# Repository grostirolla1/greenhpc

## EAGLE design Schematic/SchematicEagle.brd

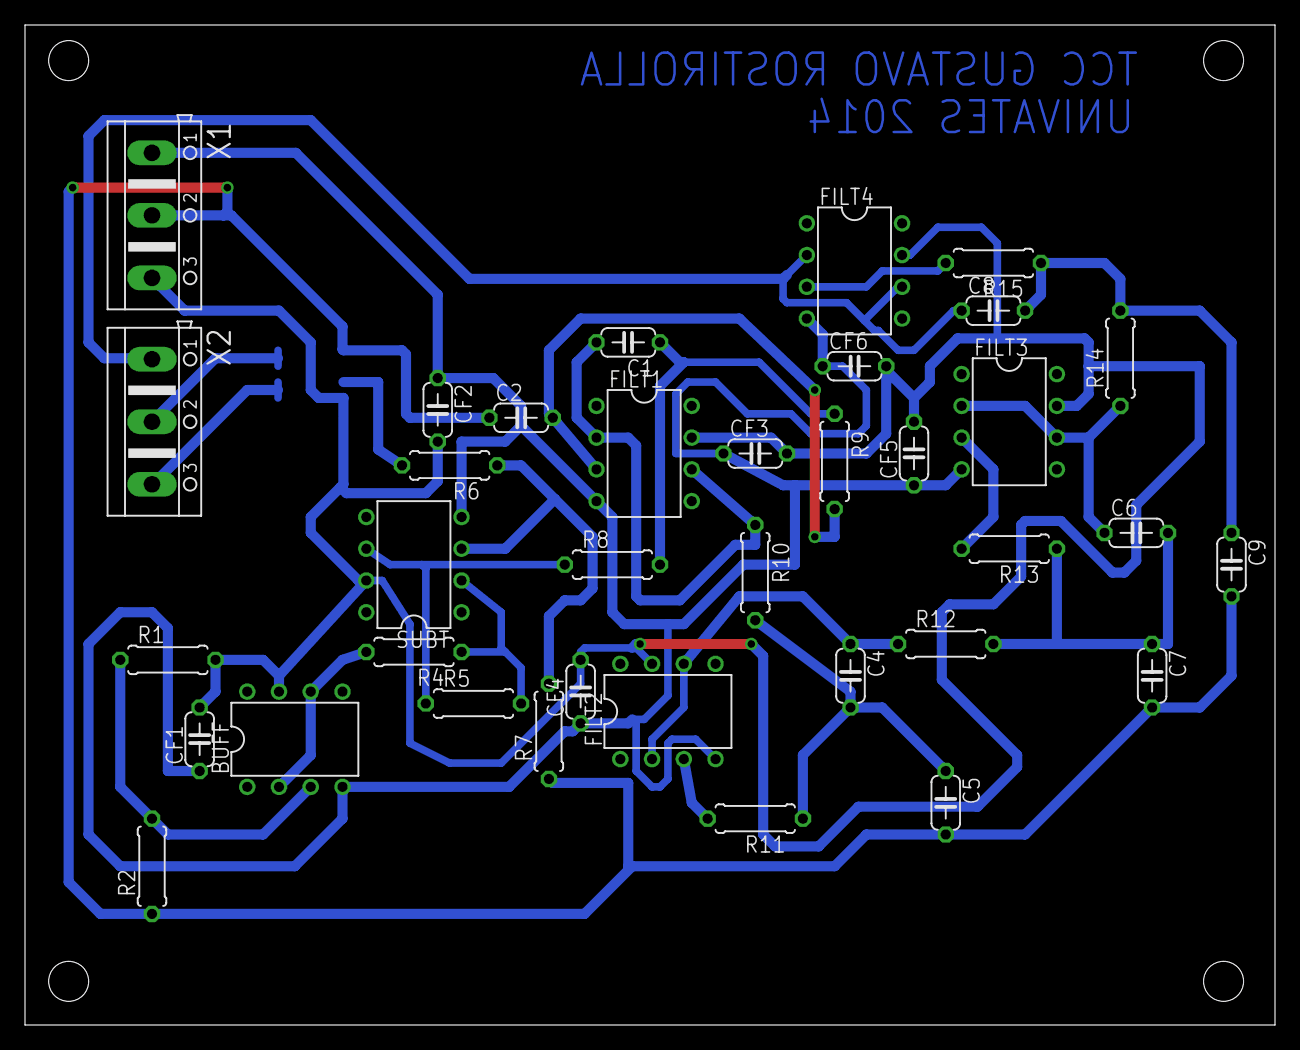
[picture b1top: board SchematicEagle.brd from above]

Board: 2 copper layers, 100.0 x 80.0 mm, 37 parts (1 on the bottom side), 23 nets.

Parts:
BUFF: OP07DN; DIL08
C1, C4: 15nF; C050-024X044
C2, C5, C7, C9: 10nF; C050-024X044
C6: 33nF; C050-024X044
C8: 330nF; C050-024X044
CF1, CF2, CF3, CF4, CF5, CF6: 100nF; C050-024X044
FILT1, FILT2, FILT3, FILT4: OP07DN; DIL08
R1, R2, R12: 10K; 0207/7
R4, R5, R6, R7: 20K; 0207/7
R8: 8,2K; 0207/7
R9: 33K; 0207/7
R10: 15K; 0207/7
R11: 18K; 0207/7
R13: 12K; 0207/7
R14: 2.2K; 0207/7
R15: 5.6K; 0207/7
SUBT: OP07DN; DIL08
U$1: ACS712; SO08
X1, X2: AK500/3

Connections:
+IP_S: U$1.1, U$1.2, X2.3
+VCC: BUFF.7, CF1.2, CF2.2, CF3.2, CF4.2, CF5.2, CF6.2, FILT1.7, FILT2.7, FILT3.7, FILT4.7, R1.2, SUBT.7, U$1.8, X1.3
-IP_S: U$1.3, U$1.4, X2.2
-VCC: BUFF.4, CF1.1, CF2.1, CF3.1, CF4.1, CF5.1, CF6.1, FILT1.4, FILT2.4, FILT3.4, FILT4.4, SUBT.4, X1.1
GND: C2.1, C5.2, C7.2, C9.2, R2.1, R7.1, U$1.5, X1.2
IN_F: R5.1, R8.1, SUBT.6
unnamed: BUFF.3, R1.1, R2.2
unnamed: C1.1, R8.2, R9.1
unnamed: R4.1, R5.2, SUBT.2
unnamed: C2.2, FILT1.3, R9.2
unnamed: R6.1, R7.2, SUBT.3
unnamed: C1.2, FILT1.2, FILT1.6, R10.1
unnamed: BUFF.2, BUFF.6, R4.2
unnamed: C4.2, C5.1, R10.2, R11.1
unnamed: C4.1, FILT2.2, FILT2.6, R12.1
unnamed: FILT2.3, R11.2
unnamed: C6.2, C7.1, R12.2, R13.1
unnamed: C6.1, FILT3.2, FILT3.6, R14.1
unnamed: FILT3.3, R13.2
unnamed: C8.2, C9.1, R14.2, R15.1
unnamed: FILT4.3, R15.2
OUT_F: C8.1, FILT4.2, FILT4.6, X2.1
OUT_I: R6.2, U$1.7

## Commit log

2014-11-27 Create gh-pages branch via GitHub
2014-11-27 Files Added

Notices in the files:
parts and their libraries:
1_SparkFun: Licensing: CC v3.0 Share-Alike You are welcome to use this library for commercial purposes.
